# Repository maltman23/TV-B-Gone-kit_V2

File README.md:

# TV-B-Gone Kit V2

The original (V1.2) <a href="http://www.adafruit.com/products/73">TV-B-Gone kit</a> is still available at Adafruit.  
  
I am currently working on a new (V2) TV-B-Gone kit. I am now on the second iteration, using a small-form ESP32 board, making it easier to solder, and easier to re-program for total beginners. This new version also uses a MOSFET, which allows for fewer parts, and allows for a longer range for turning off TVs in public places!  
  
Photo of a completed first draft of the kit, for giving workshops:  

## Project Info  
  
Imagine a dystopian future, filled with monitors, marketing at us everywhere we go. Sadly, we are living that future now. This kit is super useful, not only for yourself, but for everyone! And while maybe that's dramatic, the TV-B-Gone is perfect for playing pranks on your friends during the Super Bowl or getting some peace and quiet during dinner.  
  
The TV-B-Gone is a kit that, when soldered together, allows you to turn off almost any television within 50 meters or more.  It works on 287 total power codes - 142 American/Asian and another 145 European/African codes.  You can select which zone with a button push.  

This is an unassembled kit which means that soldering is required - but it's very easy and a great introduction to soldering in general.  The kit is powered by 3x AA batteries - that aren't included - and the output comes from 2x narrow beam IR LEDs and 2x wide-beam IR LEDs.  
  
The TV-B-Gone covers almost any television from the brands listed below, including the latest LCDs.  
  
Here is a (partial) list of the brands of monitors that the TV-B-Gone kit V2 will turn off!  
  
Acer, Admiral, Aiko, Alleron, Anam National, AOC, Apex, Baur, Bell&Howell, Brillian, Bush, Candle, Citizen, Contec, Cony, Crown, Curtis Mathes, Daiwoo, Dimensia, Electrograph, Electrohome, Emerson, Fisher, Fujitsu, Funai, Gateway, GE, Goldstar, Grundig, Grunpy, Hisense, Hitachi, Infinity, JBL, JC Penney, JVC, LG, Logik, Loewe, LXI, Majestic, Magnavox, Marantz, Maxent, Memorex, Mitsubishi, MGA, Montgomery Ward, Motorola, MTC, NEC, Neckermann, NetTV, Nikko, NTC, Otto Versand, Palladium, Panasonic, Philco, Philips, Pioneer, Portland, Proscan, Proton, Pulsar, Pye, Quasar, Quelle, Radio Shack, Realistic, RCA, Samsung, Sampo, Sansui, Sanyo, Scott, Sears, SEI, Sharp, Signature, Simpson, Sinudyne, Sonolor, Sony, Soundesign, Sylviana, Tatung, TCL, Teknika, Thompson, Toshiba, Universum, Viewsonic, Wards, White Westinghouse, Zenith  
  
## MicroPython firmware

A [MicroPython module and installation guide](firmware/micropython/README.md)
are available for the ESP32-C3 Super Mini kit, with the same NA/EU code database,
button controls and hardware-timed IR transmission.

From this directory, run `just setup` once and `just devices` to find the board.
Follow the installation guide to download MicroPython v1.29.0, then run
`just flash PORT IMAGE.bin` to erase the board and install it. Run
`just upload PORT` to build, copy the application files and restart the board.
For later application updates, run `just upload PORT` again. Run `just` to list
all commands.

## Future Ideas/Plans  
  
* Add an IR receiver for learning new OFF-Codes (the r2 of the PCB has pads for the IR receiver, but no firmware, yet) 
* Make use of the ESP32's web-server to create a web-browser interface for updating the TV-B-Gone firmware  
* Use the web-browser interface for TV-B-Gone users to share new OFF-Codes  
* Maybe make use of the ESP32's BLE abilities and create an app for smartphones to use (though, at this point I'm not sure what for)

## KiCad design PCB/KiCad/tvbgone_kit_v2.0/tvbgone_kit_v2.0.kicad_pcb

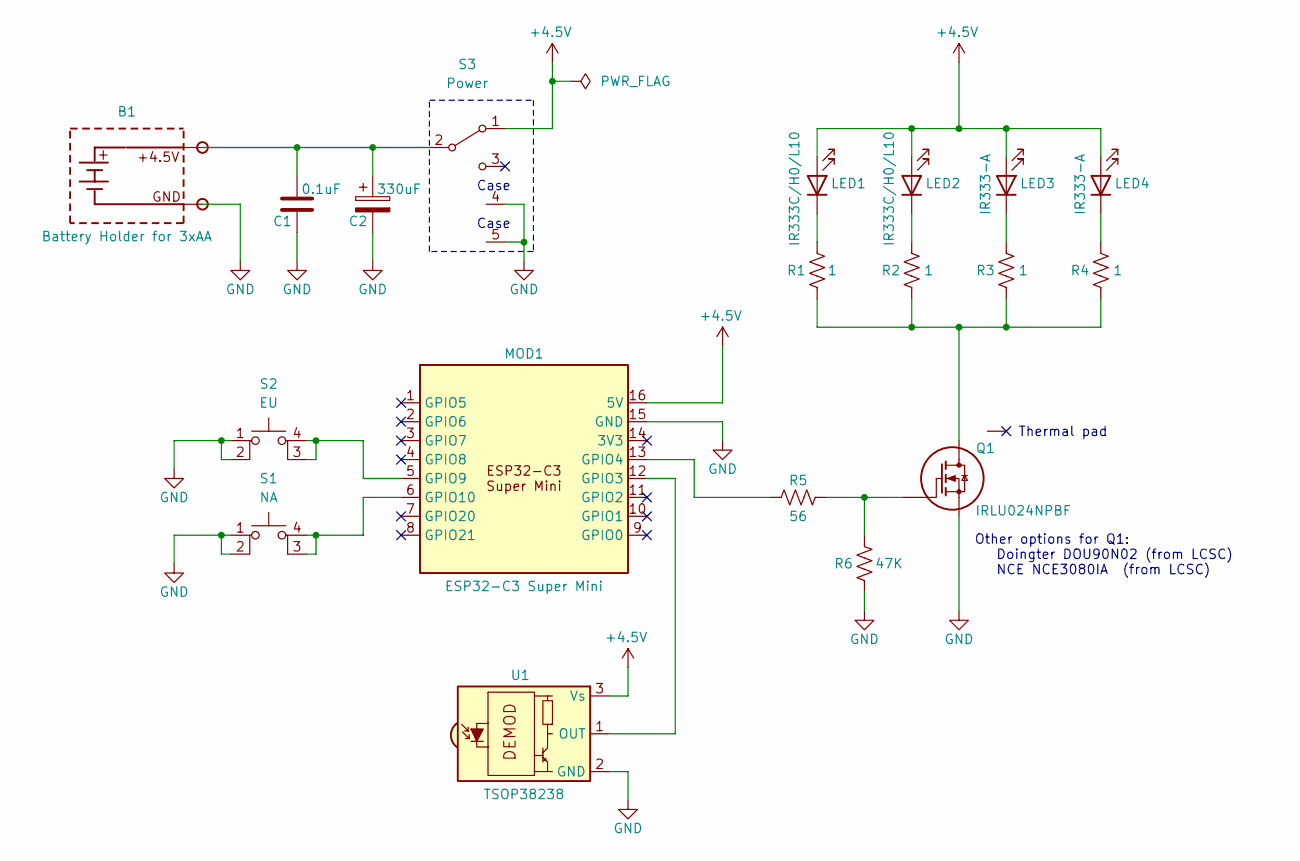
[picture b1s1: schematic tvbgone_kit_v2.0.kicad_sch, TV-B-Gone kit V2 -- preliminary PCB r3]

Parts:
B1: Battery Holder for 3xAA; BatteryHolder_Eagle_Plastic_Devices_3xAA; Part # Keystone -- 2464
C1: 0.1uF; Cap_Kemet_2.54_MLCC_through-hole; Part # Kemet -- C320C104M5R5TA7303
C2: 330uF; Cap_Panasonic_Electrolytic_8mm; Part # Panasonic -- ECE-A0JKA331
LED1, LED2: IR333C/H0/L10; LED_IR_5MM; Part # Everlight -- IR333C/H0/L10/TR1-7(R)
LED3: IR333-A; LED_IR_5MM; Part # Everlight -- IR333-A
LED4: IR333-A; LED_IR_5MM; Part # Everlight -- IR333C/H0/L10/TR1-7(R)
MOD1: ESP32-C3 Super Mini; ESP32-C3_Super_Mini; Part # Shop1102186190 Aliexpress Store, with C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
Q1: IRLU024NPBF; TO-251AA_Horizontal_TabDown; Part # Infineon -- IRLU024NPBF
R1, R2, R3, R4: 1; Resistor_THT_0.5W; Part # Stackpole -- CFM12JT1R00
R5: 56; Resistor_THT_0.25W; Part # Stackpole -- CF14JT56R0
R6: 47K; Resistor_THT_0.25W; Part # Stackpole -- CF14JT47K0
S1: NA; TACTILE_SWITCH_12MM; Part # Omron -- B3F-4005
S2: EU; TACTILE_SWITCH_12MM; Part # Omron -- B3F-4000
S3: Power; C&K_SPST_OS102011MS2QS1; Part # OS102011MS2QN1
U1: TSOP38238; Vishay_MINICAST-3Pin; Part # Vishay -- TSOP38238

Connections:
+4.5V: LED1.A, LED2.A, LED3.A, LED4.A, MOD1.16 (5V), S3.1 (A), U1.3 (Vs)
GND: B1.-, C1.2, C2.2, MOD1.15 (GND), Q1.S, R6.P$1, S1.1, S1.2, S2.1, S2.2, S3.4 (Case), S3.5 (Case), U1.2 (GND)
unnamed: LED1.K, R1.P$2
unnamed: LED2.K, R2.P$2
unnamed: LED3.K, R3.P$2
unnamed: LED4.K, R4.P$2
unnamed: MOD1.12 (GPIO3), U1.1 (OUT)
unnamed: MOD1.13 (GPIO4), R5.P$1
unnamed: MOD1.5 (GPIO9), S2.3 (K), S2.4 (A)
unnamed: MOD1.6 (GPIO10), S1.3 (K), S1.4 (A)
unnamed: Q1.D, R1.P$1, R2.P$1, R3.P$1, R4.P$1
unnamed: Q1.G, R5.P$2, R6.P$2
unnamed: B1.+, C1.1, C2.1, S3.2 (B)

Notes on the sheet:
Thermal pad
Case
Other options for Q1: Doingter DOU90N02 (from LCSC) NCE NCE3080IA (from LCSC)

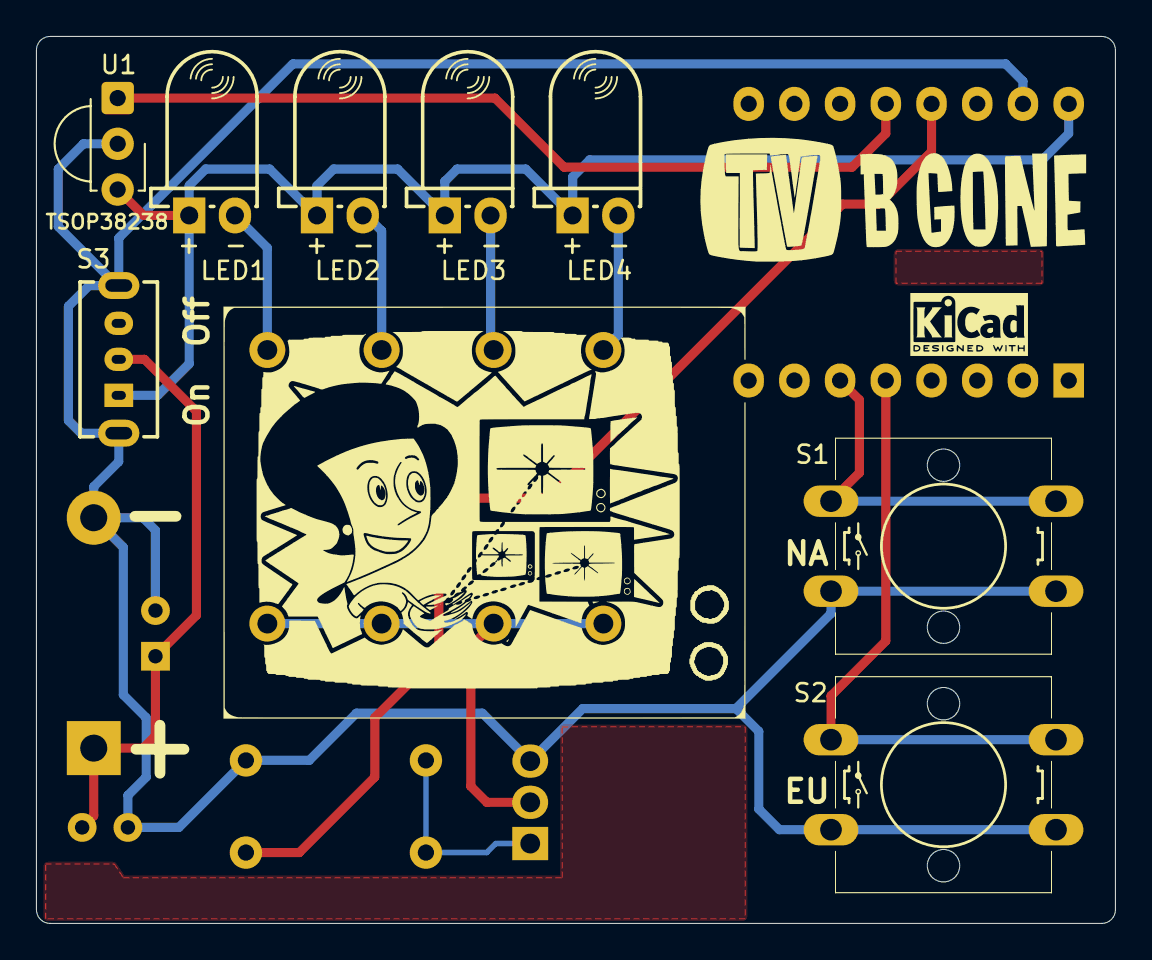
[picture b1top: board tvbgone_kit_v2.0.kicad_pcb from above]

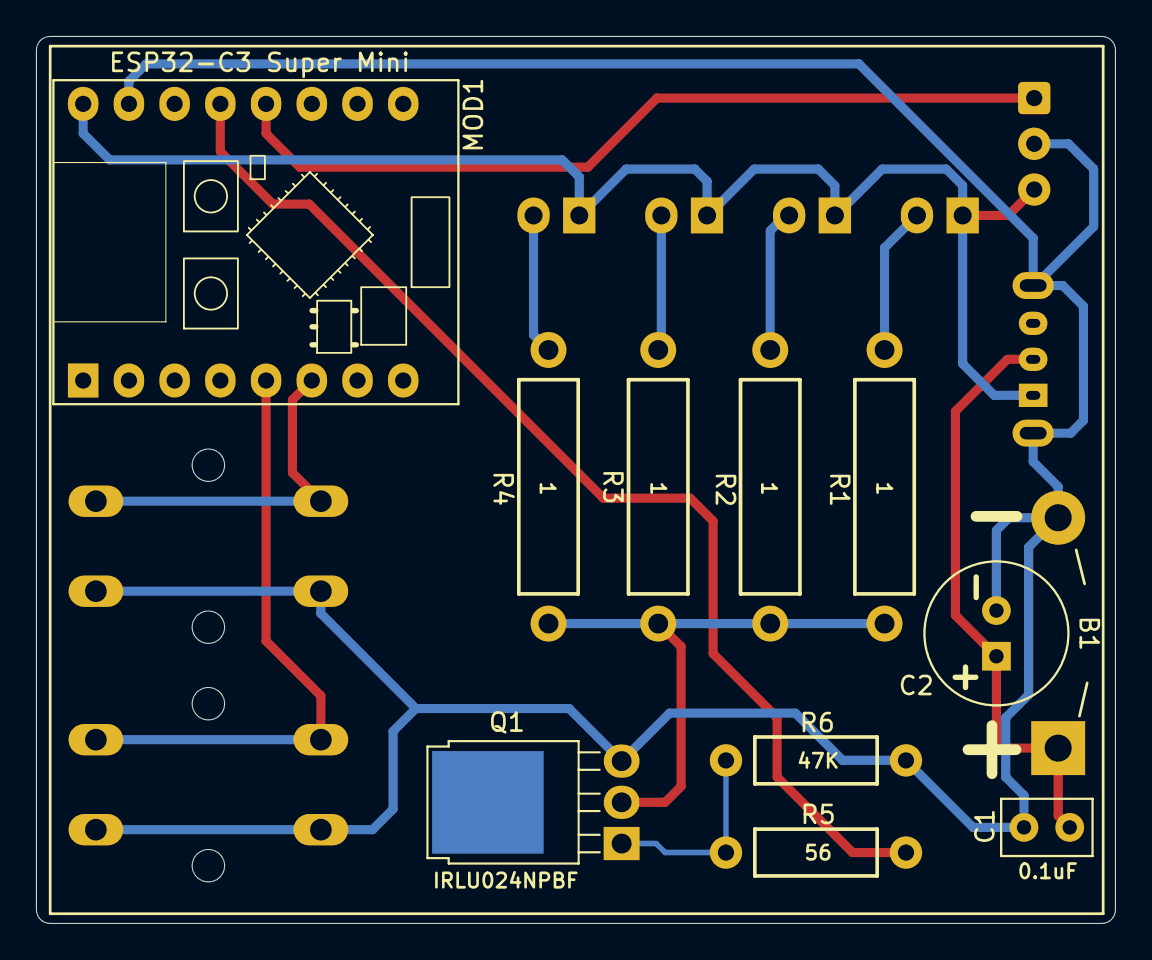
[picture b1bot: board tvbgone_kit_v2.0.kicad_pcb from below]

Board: 2 copper layers, 59.9 x 49.3 mm, 19 parts (11 on the bottom side), 13 nets.

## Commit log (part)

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2026-01-23 Update README.md
    added photo and graphic
2026-01-29 Update README.md
    Show model of the preliminary PCB 3D model.
    Add section for future ideas/plans.
2026-01-29 Add preliminary version of the kit
    Add preliminary version of the kit, including PCB and BOM
2026-04-05 Changed resistor values to prevent LED burnout on high current supply. Cleaned up the built board look by moving references inside footprints. Reduced font size from 1 -> 0.75 on some components to f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
2026-04-30 add gitignore
    add gitignore
2026-04-30 draft r2: IR LEDs on GPIO4
    * Changed IR LEDs from GPIO2 to GPIO4 (since GPIO2 goes High during bootloader programming, burning out the IR LEDs).
    * Fixed label reversal of R5 and R6
    * Cleaned up some silk screen
    * Added IR Receiver for learning IR codes (but firmware not implemented).
2026-04-30 Update README.md
    Added info about draft r2
2026-04-30 Update to KiCad10, add PDFs
    * Updated to KiCad10
    * Added PDFs for front and back of PCB for r2.
    * Added PDF for schematic for r2.
2026-04-30 add .history to gitignore
2026-05-11 fix minor zonefill mistake
    The zonefill for the background of "kit V2.0 r2" was a little too small, and it cut off the right-most edge of the right-most "2" -- expanded zonefill to fix this minor error.
2026-05-14 new IR LED resistors, updated BOM & assembly
    * After testing, R1-R4 were reduced to 1 Ohm to maximize range of IR LEDs.
    * Updated BOM.
    * Put Gerber files in their own subdirectory.
2026-05-15 Assembly instructions use 1 Ohm for R1-R4
    Update assembly instructions to reflect using 1 Ohm resistors.
2026-05-19 minor update to comments
    Updated the comments describing the hardware to reflect the most recent hardware.
2026-05-24 updated assembly instructions to r2 PCB
    Updated assembly instructions for r2 PCB
2026-06-26 Change C2 to 0.1" lead-spacing
    Change C2 to 0.1" lead-spacing
    C2 part number changed from Panasonic ECE-A0JKA331Q to Panasonic ECE-A0JKA331

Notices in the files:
PCB/KiCad/tvbgone_kit_v2.0/tvbgone_kit_v2.0.kicad_pcb:
License:  CC BY-SA 4.0
